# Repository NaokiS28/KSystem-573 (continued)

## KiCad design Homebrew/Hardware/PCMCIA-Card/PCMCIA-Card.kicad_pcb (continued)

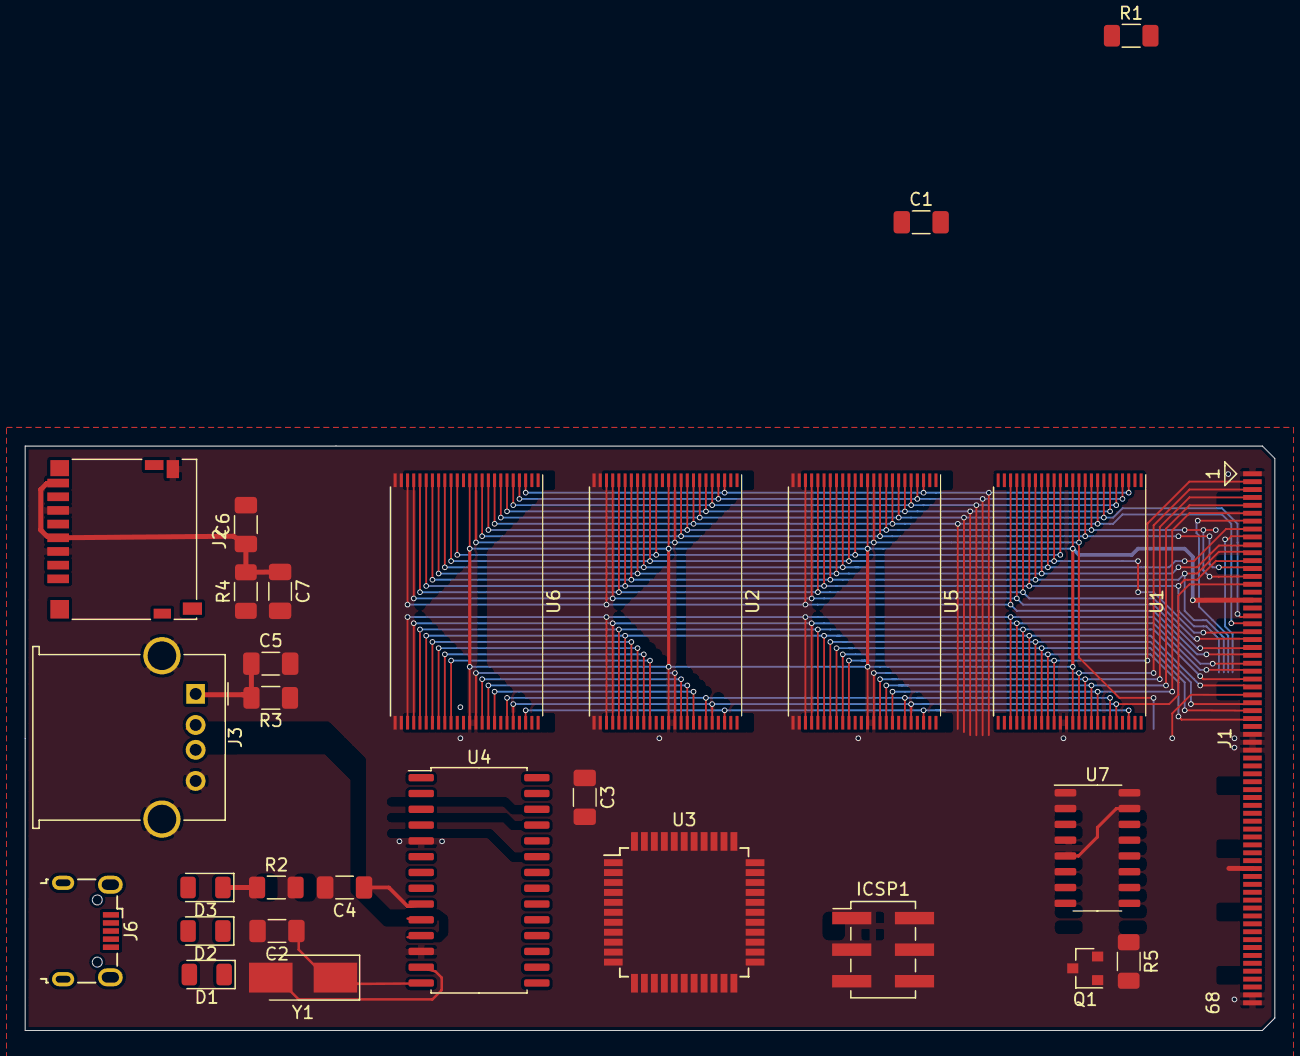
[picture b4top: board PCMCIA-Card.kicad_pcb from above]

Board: 2 copper layers, 100.5 x 47.0 mm, 29 parts (0 on the bottom side), 67 nets.

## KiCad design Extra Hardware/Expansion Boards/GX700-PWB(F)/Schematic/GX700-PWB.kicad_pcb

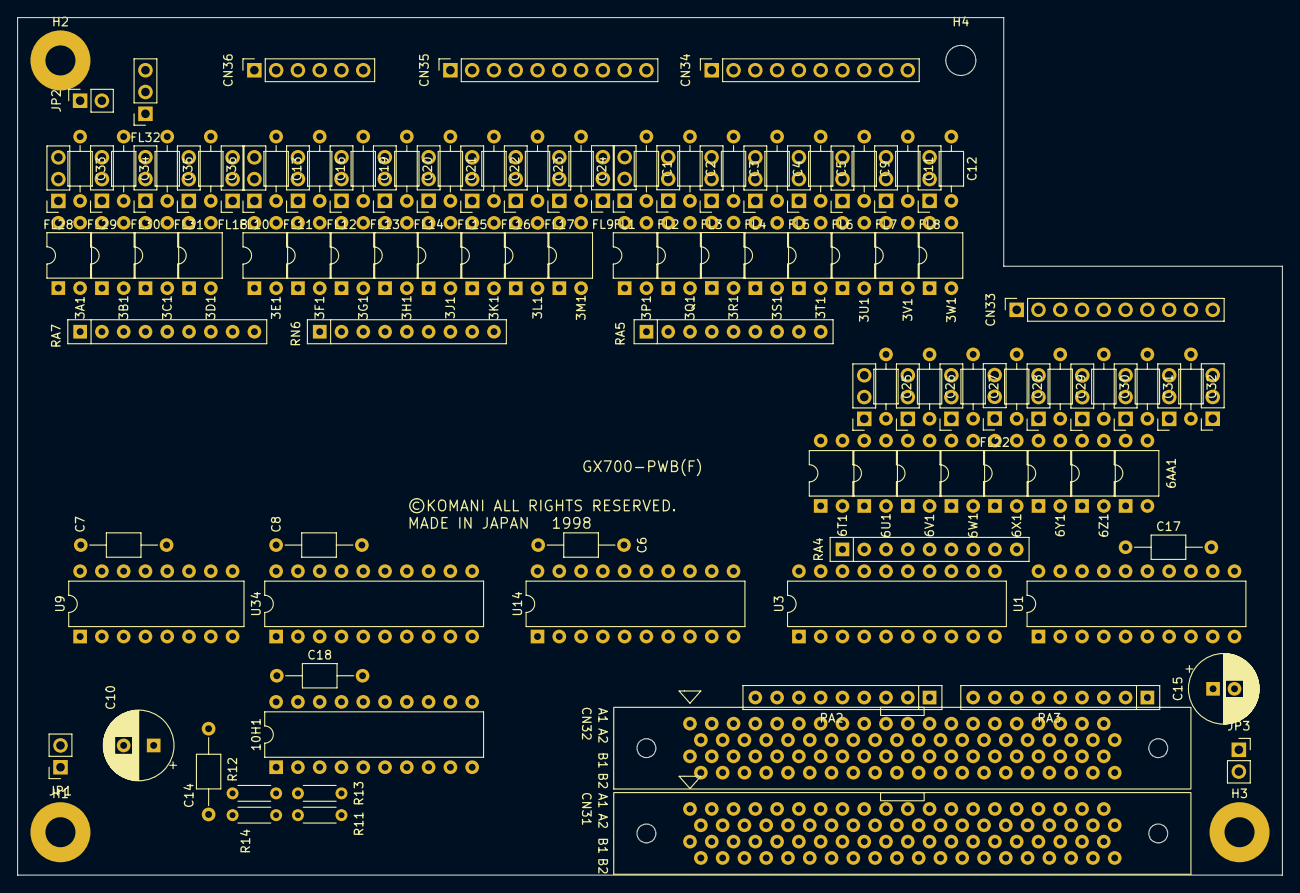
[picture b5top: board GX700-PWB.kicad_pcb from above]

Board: 2 copper layers, 147.5 x 100.0 mm, 125 parts (0 on the bottom side), 184 nets, no tracks yet.

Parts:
3A1, 3B1, 3C1, 3D1, 3E1, 3F1, 3G1, 3H1, 3J1, 3K1, 3L1, 3M1, 3P1, 3Q1, 3R1, 3S1, 3T1, 3U1, 3V1, 3W1, 6AA1, 6T1, 6U1, 6V1, 6W1, 6X1, 6Y1, 6Z1: PC817; DIP-4_W7.62mm
10H1: GAL16V8 (X700F1); DIP-20_W7.62mm
C1, C2, C3, C4, C5, C9, C11, C12, C13, C16, C19, C20, C21, C22, C23, C24, C25, C26, C27, C28, C29, C30, C31, C32, C33, C34, C35, C36: 20n; C_Axial_L3.8mm_D2.6mm_P7.50mm_Horizontal
C6, C7, C8, C14, C17, C18: 1uf; C_Axial_L3.8mm_D2.6mm_P10.00mm_Horizontal
C10: 330u16v; CP_Radial_D8.0mm_P3.50mm
C15: 330u16v; CP_Radial_D8.0mm_P2.50mm
CN31, CN32: 573_EXP; JAE-TX15-80P
CN33, CN34, CN35: B10PSHF1A; PinSocket_1x10_P2.54mm_Vertical
CN36: B6PSHF1AA; PinSocket_1x06_P2.54mm_Vertical
FL1, FL2, FL3, FL4, FL5, FL6, FL7, FL8, FL9, FL10, FL11, FL12, FL13, FL14, FL15, FL16, FL17, FL18, FL19, FL20, FL21, FL22, FL23, FL24, FL25, FL26, FL27, FL28, FL29, FL30, FL31, FL32: EMI_Filter_LCL; PinSocket_1x03_P2.54mm_Vertical
H1, H2, H3: MountingHole_Pad; MountingHole_3.5mm_Pad
H4: MountingHole; MountingHole_3.5mm
JP1, JP2, JP3: Jumper_2_Open; PinSocket_1x02_P2.54mm_Vertical
R11, R12, R13, R14: 4.7k; R_Axial_DIN0204_L3.6mm_D1.6mm_P5.08mm_Horizontal
RA2, RA3: 4.7k; R_Array_SIP9
RA4, RA5, RA7: 470; R_Array_SIP9
RN6: 470; R_Array_SIP9
U1: 74LS244; DIP-20_W7.62mm
U3, U14, U34: 74LS273; DIP-20_W7.62mm
U9: 74LS175; DIP-16_W7.62mm

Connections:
573-A0: CN31.a24 (A0), CN32.a24 (A0)
573-A1: CN31.b24 (A1), CN32.b24 (A1)
573-A2: CN31.a23 (A2), CN32.a23 (A2)
573-A3: 10H1.9 (I9), CN31.b23 (A3), CN32.b23 (A3), RA2.2 (R1)
573-A4: 10H1.8 (I8), CN31.a22 (A4), CN32.a22 (A4), RA2.3 (R2)
573-A5: 10H1.7 (I7), CN31.b22 (A5), CN32.b22 (A5), RA2.4 (R3)
573-A6: 10H1.6 (I6), CN31.a21 (A6), CN32.a21 (A6), RA2.5 (R4)
573-A7: 10H1.5 (I5), CN31.b21 (A7), CN32.b21 (A7), RA2.6 (R5)
573-A12: CN31.a20 (A12), CN32.a20 (A12)
573-A13: CN31.b20 (A13), CN32.b20 (A13)
573-A14: CN31.a19 (A14), CN32.a19 (A14)
573-A15: CN31.b19 (A15), CN32.b19 (A15)
573-A20: CN31.a18 (A20), CN32.a18 (A20)
573-A21: CN31.b18 (A21), CN32.b18 (A21)
573-A22: CN31.a17 (A22), CN32.a17 (A22)
573-A23: CN31.b17 (A23), CN32.b17 (A23)
573-D0: CN31.a32 (D0), CN32.a32 (D0), RA3.2 (R1), U1.17 (I3b)
573-D1: CN31.b32 (D1), CN32.b32 (D1), RA3.3 (R2), U1.15 (I2b)
573-D2: CN31.a31 (D2), CN32.a31 (D2), RA3.4 (R3), U1.13 (I1b)
573-D3: CN31.b31 (D3), CN32.b31 (D3), RA3.5 (R4), U1.11 (I0b)
573-D4: CN31.a30 (D4), CN32.a30 (D4), RA3.6 (R5), U1.8 (I3a)
573-D5: CN31.b30 (D5), CN32.b30 (D5), RA3.7 (R6), U1.6 (I2a)
573-D6: CN31.a29 (D6), CN32.a29 (D6), RA3.8 (R7), U1.4 (I1a)
573-D7: CN31.b29 (D7), CN32.b29 (D7), RA3.9 (R8), U1.2 (I0a)
573-D8: CN31.a28 (D8), CN32.a28 (D8)
573-D9: CN31.b28 (D9), CN32.b28 (D9)
573-D10: CN31.a27 (D10), CN32.a27 (D10)
573-D11: CN31.b27 (D11), CN32.b27 (D11)
573-D12: CN31.a26 (D12), CN32.a26 (D12)
573-D13: CN31.b26 (D13), CN32.b26 (D13)
573-D14: CN31.a25 (D14), CN32.a25 (D14)
573-D15: CN31.b25 (D15), CN32.b25 (D15)
+3V3: CN31.a36 (+3V3), CN31.a37 (+3V3), CN31.a38 (+3V3), CN31.a39 (+3V3), CN31.a40 (+3V3), CN31.b36 (+3V3), CN31.b37 (+3V3), CN31.b38 (+3V3), CN31.b39 (+3V3), CN31.b40 (+3V3), CN32.a36 (+3V3), CN32.a37 (+3V3), CN32.a38 (+3V3), CN32.a39 (+3V3), CN32.a40 (+3V3), CN32.b36 (+3V3), CN32.b37 (+3V3), CN32.b38 (+3V3), CN32.b39 (+3V3), CN32.b40 (+3V3), R11.2, R14.2, RA2.1 (common), RA3.1 (common)
+5V: 10H1.20 (VCC), C6.1, C7.1, C8.1, C10.1, C14.1, C15.1, C17.1, C18.1, CN31.a1 (+5V), CN31.a2 (+5V), CN31.a3 (+5V), CN31.a4 (+5V), CN31.a5 (+5V), CN31.b1 (+5V), CN31.b2 (+5V), CN31.b3 (+5V), CN31.b4 (+5V), CN31.b5 (+5V), CN32.a1 (+5V), CN32.a2 (+5V), CN32.a3 (+5V), CN32.a4 (+5V), CN32.a5 (+5V), CN32.b1 (+5V), CN32.b2 (+5V), CN32.b3 (+5V), CN32.b4 (+5V), CN32.b5 (+5V), R12.2, R13.2, RA4.1 (common), RA5.1 (common), RA7.1 (common), RN6.1 (common), U1.20 (VCC), U3.20 (VCC), U9.16 (VCC), U14.20 (VCC), U34.20 (VCC)
DATA-0: U1.3 (O3b), U3.3 (D0), U9.4 (D0), U14.3 (D0), U34.3 (D0)
DATA-1: U1.5 (O2b), U3.4 (D1), U9.5 (D1), U14.4 (D1), U34.4 (D1)
DATA-2: U1.7 (O1b), U3.7 (D2), U9.12 (D2), U14.7 (D2), U34.7 (D2)
DATA-3: U1.9 (O0b), U3.8 (D3), U9.13 (D3), U14.8 (D3), U34.8 (D3)
DATA-4: U1.12 (O3a), U3.13 (D4), U14.13 (D4), U34.13 (D4)
DATA-5: U1.14 (O2a), U3.14 (D5), U14.14 (D5), U34.14 (D5)
DATA-6: U1.16 (O1a), U3.17 (D6), U14.17 (D6), U34.17 (D6)
DATA-7: U1.18 (O0a), U3.18 (D7), U14.18 (D7), U34.18 (D7)
DREQ5: CN31.a14 (DREQ5), CN32.a14 (DREQ5)
DREQ5-2: CN31.b12 (DREQ5), CN32.b12 (DREQ5)
EXP-15: CN31.b15 (N/C), CN32.b15 (N/C)
GND: 10H1.10 (GND), 10H1.11 (I10/~OE), C6.2, C7.2, C8.2, C10.2, C14.2, C15.2, C17.2, C18.2, CN31.a8 (GND), CN31.a9 (GND), CN31.a11 (GND), CN31.a13 (GND), CN31.a33 (GND), CN31.a34 (GND), CN31.a35 (GND), CN31.b7 (GND), CN31.b9 (GND), CN31.b11 (GND), CN31.b13 (GND), CN31.b33 (GND), CN31.b34 (GND), CN31.b35 (GND), CN32.a8 (GND), CN32.a9 (GND), CN32.a11 (GND), CN32.a13 (GND), CN32.a33 (GND), CN32.a34 (GND), CN32.a35 (GND), CN32.b7 (GND), CN32.b9 (GND), CN32.b11 (GND), CN32.b13 (GND), CN32.b33 (GND), CN32.b34 (GND), CN32.b35 (GND), JP1.1 (A), JP2.1 (A), U1.1 (OEa), U1.10 (GND), U1.19 (OEb), U3.10 (GND), U9.8 (GND), U14.10 (GND), U34.10 (GND)
IRQ10: CN31.a16 (IRQ10), CN32.a16 (IRQ10)
IRQ10-2: CN31.b16 (IRQ10), CN32.b16 (IRQ10)
ISOLATED-COMMON: CN35.10, CN36.6, FL1.2, FL2.2, FL3.2, FL4.2, FL5.2, FL6.2, FL7.2, FL8.2, FL9.2, FL10.2, FL11.2, FL12.2, FL13.2, FL14.2, FL15.2, FL16.2, FL17.2, FL18.2, FL19.2, FL20.2, FL21.2, FL22.2, FL23.2, FL24.2, FL25.2, FL26.2, FL27.2, FL28.2, FL29.2, FL30.2, FL31.2, FL32.2, JP3.1 (A)
unnamed: 3A1.1, RA7.2 (R1)
unnamed: 3A1.2, U9.15 (Q3)
unnamed: 3A1.3, 3B1.3, 3C1.3, 3D1.3, C33.1, C34.1, C35.1, C36.1, FL32.1
unnamed: 3A1.4, C33.2, FL28.1
unnamed: 3B1.1, RA7.3 (R2)
unnamed: 3B1.2, U9.10 (Q2)
unnamed: 3B1.4, C34.2, FL29.1
unnamed: 3C1.1, RA7.4 (R3)
unnamed: 3C1.2, U9.7 (Q1)
unnamed: 3C1.4, C35.2, FL30.1
unnamed: 3D1.1, RA7.5 (R4)
unnamed: 3D1.2, U9.2 (Q0)
unnamed: 3D1.4, C36.2, FL31.1
unnamed: 3E1.1, RN6.2 (R1)
unnamed: 3E1.2, U34.19 (Q7)
unnamed: 3E1.3, 3F1.3, 3G1.3, 3H1.3, 3J1.3, 3K1.3, 3L1.3, 3M1.3, C13.1, C16.1, C19.1, C20.1, C21.1, C22.1, C23.1, C24.1, FL18.1
unnamed: 3E1.4, C13.2, FL10.1
unnamed: 3F1.1, RN6.3 (R2)
unnamed: 3F1.2, U34.2 (Q0)
unnamed: 3F1.4, C16.2, FL11.1
unnamed: 3G1.1, RN6.4 (R3)
unnamed: 3G1.2, U34.16 (Q6)
unnamed: 3G1.4, C19.2, FL12.1
unnamed: 3H1.1, RN6.5 (R4)
unnamed: 3H1.2, U34.5 (Q1)
unnamed: 3H1.4, C20.2, FL13.1
unnamed: 3J1.1, RN6.6 (R5)
unnamed: 3J1.2, U34.15 (Q5)
unnamed: 3J1.4, C21.2, FL14.1
unnamed: 3K1.1, RN6.7 (R6)
unnamed: 3K1.2, U34.6 (Q2)
unnamed: 3K1.4, C22.2, FL15.1
unnamed: 3L1.1, RN6.8 (R7)
unnamed: 3L1.2, U34.12 (Q4)
unnamed: 3L1.4, C23.2, FL16.1
unnamed: 3M1.1, RN6.9 (R8)
unnamed: 3M1.2, U34.9 (Q3)
unnamed: 3M1.4, C24.2, FL17.1
unnamed: 3P1.1, RA5.2 (R1)
unnamed: 3P1.2, U14.19 (Q7)
unnamed: 3P1.3, 3Q1.3, 3R1.3, 3S1.3, 3T1.3, 3U1.3, 3V1.3, 3W1.3, C1.1, C2.1, C3.1, C4.1, C5.1, C9.1, C11.1, C12.1, FL9.1
unnamed: 3P1.4, C1.2, FL1.1
unnamed: 3Q1.1, RA5.3 (R2)
unnamed: 3Q1.2, U14.2 (Q0)
unnamed: 3Q1.4, C2.2, FL2.1
unnamed: 3R1.1, RA5.4 (R3)
unnamed: 3R1.2, U14.16 (Q6)
unnamed: 3R1.4, C3.2, FL3.1
unnamed: 3S1.1, RA5.5 (R4)
unnamed: 3S1.2, U14.5 (Q1)
unnamed: 3S1.4, C4.2, FL4.1
unnamed: 3T1.1, RA5.6 (R5)
unnamed: 3T1.2, U14.15 (Q5)
unnamed: 3T1.4, C5.2, FL5.1
unnamed: 3U1.1, RA5.7 (R6)
unnamed: 3U1.2, U14.6 (Q2)
unnamed: 3U1.4, C9.2, FL6.1
unnamed: 3V1.1, RA5.8 (R7)
unnamed: 3V1.2, U14.12 (Q4)
unnamed: 3V1.4, C11.2, FL7.1
unnamed: 3W1.1, RA5.9 (R8)
unnamed: 3W1.2, U14.9 (Q3)
unnamed: 3W1.4, C12.2, FL8.1
unnamed: 6AA1.1, RA4.9 (R8)
unnamed: 6AA1.2, U3.9 (Q3)
unnamed: 6AA1.4, C32.2, FL26.1
unnamed: 6T1.1, RA4.2 (R1)
unnamed: 6T1.2, U3.19 (Q7)
unnamed: 6AA1.3, 6T1.3, 6U1.3, 6V1.3, 6W1.3, 6X1.3, 6Y1.3, 6Z1.3, C25.1, C26.1, C27.1, C28.1, C29.1, C30.1, C31.1, C32.1, FL27.1
unnamed: 6T1.4, C25.2, FL19.1
unnamed: 6U1.1, RA4.3 (R2)
unnamed: 6U1.2, U3.2 (Q0)
unnamed: 6U1.4, C26.2, FL20.1
unnamed: 6V1.1, RA4.4 (R3)
unnamed: 6V1.2, U3.16 (Q6)
unnamed: 6V1.4, C27.2, FL21.1
unnamed: 6W1.1, RA4.5 (R4)
unnamed: 6W1.2, U3.5 (Q1)
unnamed: 6W1.4, C28.2, FL22.1
unnamed: 6X1.1, RA4.6 (R5)
unnamed: 6X1.2, U3.15 (Q5)
unnamed: 6X1.4, C29.2, FL23.1
unnamed: 6Y1.1, RA4.7 (R6)
unnamed: 6Y1.2, U3.6 (Q2)
unnamed: 6Y1.4, C30.2, FL24.1
unnamed: 6Z1.1, RA4.8 (R7)
unnamed: 6Z1.2, U3.12 (Q4)
unnamed: 6Z1.4, C31.2, FL25.1
unnamed: CN33.1, CN33.10, FL27.3
unnamed: CN33.2, FL19.3
unnamed: CN33.3, FL20.3
unnamed: CN33.4, FL21.3
unnamed: CN33.5, FL22.3
unnamed: CN33.6, FL23.3
unnamed: CN33.7, FL24.3
unnamed: CN33.8, FL25.3
unnamed: CN33.9, FL26.3
unnamed: CN34.1, CN34.10, FL9.3
unnamed: CN34.2, FL1.3
unnamed: CN34.3, FL2.3
unnamed: CN34.4, FL3.3
unnamed: CN34.5, FL4.3
unnamed: CN34.6, FL5.3
unnamed: CN34.7, FL6.3
unnamed: CN34.8, FL7.3
unnamed: CN34.9, FL8.3
unnamed: CN35.1, FL18.3
unnamed: CN35.2, FL10.3
unnamed: CN35.3, FL11.3
unnamed: CN35.4, FL12.3
unnamed: CN35.5, FL13.3
unnamed: CN35.6, FL14.3
unnamed: CN35.7, FL15.3
unnamed: CN35.8, FL16.3
unnamed: CN35.9, FL17.3
unnamed: CN36.1, FL32.3
unnamed: CN36.2, FL28.3
unnamed: CN36.3, FL29.3
unnamed: CN36.4, FL30.3
unnamed: CN36.5, FL31.3
unnamed: H1.1, JP1.2 (B)
unnamed: H2.1, JP2.2 (B)
unnamed: H3.1, JP3.2 (B)
U3-CP: 10H1.13 (IO7), U3.11 (Cp)
U9-CP: 10H1.16 (IO4), U9.9 (Cp)
U14-CP: 10H1.14 (IO6), U14.11 (Cp)
U34-CP: 10H1.15 (IO5), U34.11 (Cp)
~EXP1-2: CN31.b14 (~EXP1), CN32.b14 (~EXP1)
~EXP1: CN31.a12 (~EXP1), CN32.a12 (~EXP1)
~EXP2: 10H1.1 (I1/CLK), CN31.a15 (~EXP2), CN32.a15 (~EXP2), R12.1
~READ: 10H1.2 (I2), CN31.a6 (~READ), CN32.a6 (~READ), R14.1
~RESET2: CN31.b10 (~RESET), CN32.b10 (~RESET)
~RESET: 10H1.4 (I4), CN31.a10 (~RESET), CN32.a10 (~RESET), R13.1, U3.1 (~Mr), U9.1 (~Mr), U14.1 (~Mr), U34.1 (~Mr)
~WR1: 10H1.3 (I3), CN31.b6 (~WR1), CN32.b6 (~WR1), R11.1
~WR2: CN31.a7 (~WR2), CN32.a7 (~WR2)

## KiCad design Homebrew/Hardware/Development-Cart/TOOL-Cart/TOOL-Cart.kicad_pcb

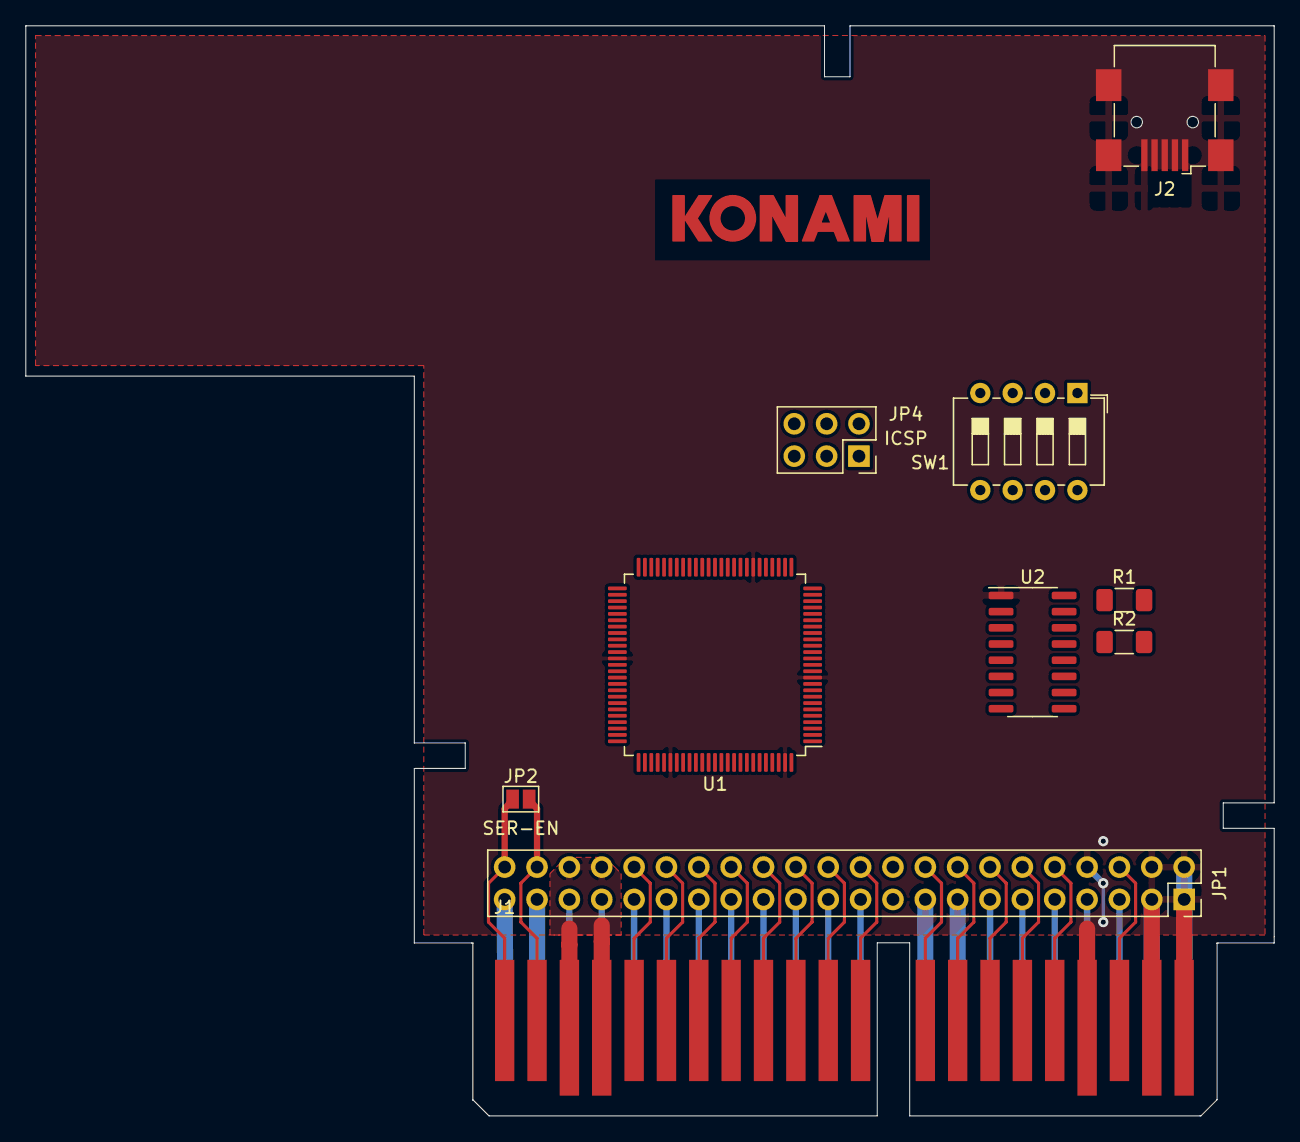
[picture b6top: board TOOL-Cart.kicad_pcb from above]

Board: 2 copper layers, 98.0 x 85.6 mm, 10 parts (0 on the bottom side), 38 nets.

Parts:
J1: Security Cart Edge; Security_Cart
J2: USB_B_Mini; USB_Mini-B_Wuerth_65100516121_Horizontal
JP1: Cart Pins; PinSocket_2x22_P2.54mm_Vertical
JP2: S-EN; SolderJumper-2_P1.3mm_Open_Pad1.0x1.5mm
JP4: ATMEGA-ICSP; PinSocket_2x03_P2.54mm_Vertical
R1, R2: 22; R_1206_3216Metric_Pad1.30x1.75mm_HandSolder
SW1: SW_DIP_x04; SW_DIP_SPSTx04_Slide_6.7x11.72mm_W7.62mm_P2.54mm_LowProfile
U1: ATmega2560-16AU; TQFP-100_14x14mm_P0.5mm
U2: CH340C; SOIC-16_3.9x9.9mm_P1.27mm

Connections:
+5V: J1.21, J1.22, J1.41, J1.42, JP1.38, JP1.40, JP1.41, JP1.43, U2.16
CART-4: J1.4, JP1.7
CART-7: J1.7, JP1.13
CART-11: J1.11, JP1.21
CART-12: J1.12, JP1.23
CART-25: J1.25, JP1.6
CART-27: J1.27, JP1.10
CART-28: J1.28, JP1.12
CART-29: J1.29, JP1.14
CART-30: J1.30, JP1.16
CART-31: J1.31, JP1.18
GND: J1.1, J1.2, J1.8, J1.9, J1.23, J1.24, J1.26, J2.5, J2.6, JP1.1, JP1.2, JP1.3, JP1.4, JP1.8, JP1.15, JP1.17, U1.11, U1.32, U1.62, U1.81, U1.99, U2.1
INPUT-0: J1.13, JP1.25, U1.97
INPUT-1: J1.14, JP1.27, U1.96
INPUT-2: J1.15, JP1.29, U1.95
INPUT-3: J1.16, JP1.31, U1.94
INPUT-4: J1.17, JP1.33, U1.93
INPUT-5: J1.18, JP1.35, U1.92
INPUT-6: J1.19, JP1.37, U1.91
INPUT-7: J1.20, JP1.39, U1.90
unnamed: J2.2, R2.2
unnamed: J2.3, R1.2
unnamed: R1.1, U2.5
unnamed: R2.1, U2.6
unnamed: U1.10, U1.31, U1.61, U1.80
OUTPUT-0: J1.40, JP1.36, U1.89
OUTPUT-1: J1.39, JP1.34, U1.88
OUTPUT-2: J1.38, JP1.32, U1.87
OUTPUT-3: J1.37, JP1.30, U1.86
OUTPUT-4: J1.36, JP1.28, U1.85
OUTPUT-5: J1.35, JP1.26, U1.84
OUTPUT-6: J1.34, JP1.24, U1.83
OUTPUT-7: J1.33, JP1.22, U1.82
RX0: J1.5, JP1.9, U2.3
SEN-1: J1.44, JP1.44, JP2.1
SEN-2: J1.43, JP1.42, JP2.2
TX0: J1.6, JP1.11, U2.2
~DSR: J1.3, JP1.5

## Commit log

2022-02-03 Initial Commit
    Not complete!!
2022-02-04 Added GE675-PWB(A)
    IO Board for Fisherman's Bait 3
2022-02-05 Update fp-info-cache
2022-02-08 Updated GE765
2022-02-08 50% Complete schematics
2022-02-08 Finished reel connector
2022-02-09 Wrote up about the E765B1 PAL
2022-02-11 More CN31 connector labels
2022-02-14 Added mostly guesswork of GX700-PWB
    The guess is based on high resolution photos, but it's not that complicated so fairly confident it's enough to build a replica. PAL is likely just deciding with latch to clock on write.
2022-02-14 Added rough draft of Stage IO board
2022-02-14 Added power input to GN845
2022-02-14 Small updates
2022-03-09 Updated Schematics
    PCMCIA is pinned out
2022-03-11 Fixed bugs
    IDE Retrace, PCMCIA checked
2022-03-12 Flash fixes, security cart done, most logic figured
2022-03-15 573 specific mostly mapped
2022-03-17 Added 3D Models
2022-09-21 Big update to the schematics
2022-09-22 Added toshiba drive
2022-09-24 Added Symbols, PSX page
    Added PSX CPU and GPU symbols, added a COH PSX skeleton schematic and also updated the JAMMA symbol and footprint as it was bad.
2022-10-16 A lot of fixes.
    Moved some libraries about to allow other schematics to share parts. 573 Expansion IO now has a proper symbol and part. JAE TX15 connector has a footprint. GX700 IO board has been fixed (output from 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
2022-10-16 Laid out GX700-PWB(F)
    Needs traces doing but the measurements are all there.
2022-10-21 Updated design
2022-11-17 Updated IO Boards and descriptions
2022-11-23 Updated GN845(B)'s schematic
    The schematic wrongly claimed there was a seperate LIGHT-GND. This is not true, it was ground, only the outer mounting holes and the LCL filters have a seperate ground (or can have one)
2023-01-05 Started mapping out Digital IO board
2023-01-17 Added basic digital IO pictures.
    Needs better ones
2023-02-05 General Fixes
2023-03-15 Updated schematics
2023-07-04 Update Working Drive List.md
    Added drives from Hydreigon
2023-07-19 Update Working Drive List.md
    New drive from Hydregion
2024-04-29 Restructuring
2025-11-19 Major board changes to give a rough render of the PCB
2025-11-19 Major PCB changes to render a nicer 3D image
2025-11-19 Flash card images
